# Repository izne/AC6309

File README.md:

# AC6309 Platform
A minimalistic industrial computer core, based on Motorola 6809 architecture.

## Purpose
Proof of concept custom 8-bit industrial computer with minimal device count implementation. Modular, low-power design, allowing easy expansion and customization per use case.

## Dedication
AC29 is dedicated to my beloved father.

## AC29 projected configuration

## Prototype build 
* CPU: HD63B09 @ 1.8432MHz
* RAM: 32KB W24257A
* ROM: 8KB 28C256 (2x ROMs)
* UART: HD63B50 (1MBps) on FT23 USB Serial
* Address decoding: 74HCT00 & 74HCT138
* Expansion: 1x 40-pin header for expansion board with 3 slots mapped at $8000, $9000 and $B000
* Power over USB

## Example physical layout

## PCB Updates
Current state of PCB design:

## System memory map
|Address range|Device|Size|
|-------------|------|----|
|$0000-$7FFF|RAM|32KB|
|$8000-$8FFF|Extension port #1|4KB|
|$9000-$9FFF|Extension port #2|4KB|
|$A000-$AFFF|UART|4KB|
|$B000-$BFFF|Extension port #3|4KB|
|$C000-$FFFF|ROM|16KB|

The 32KB of RAM is allocated from the bottom of the address range $0000 to $7FFF.
The ROM is allocated at top 8KB of the address space starting $C000 to $DFFF.

The I/O mapping is allowing compatibility with existing BIOS images having ACIA on address 0xA000. 

## Writing the ROM image
Using the combination ROM image in Intel HEX format it needs first be turned into a binary image to be written to the EEPROM.
> objcopy -I ihex -O binary combined.hex combined.bin

Write the resulting .bin file using the specially created EEPROM programmer for AT28C-series EEPROMs. Or any other.
> promdude.exe -f combined.bin

As a note, burning the combined.bin (16K) onto 32K 28C256 has to be at the correct half. Optionally, a copy of combined.bin twice into the chip will do as well.

## ROM switching
As the firmware is 16K and 28C256 (32K) chips are nowadays more accesible, two firmware images could be stored in the full 32K capacity of the chip. A ROM switching key to be implemented on the board, to switch the higher or lower part of the chip to be "visible" (A14) at boot.

## Communication
The system communicates with a terminal via USB serial connection using the included ACIA device and its UART capability, coupled with an FTDI232 header. Terminal serial port settings: 115200 baud, 8n1, no hardware handshake yet.

## Software checklist
- [x] Run ASSIST09 and Extended BASIC
- [x] Write basic program (asm)
- [x] Cross-compile on host machine
- [x] Easy program transer via ASSIST09 Load (S19)
- [ ] Use of high level C code (CMOC)

## Hardware checklist
- [x] Breadboard prototype running
- [x] Revision 1 completion and PCB fabrication
- [ ] Extended addressing ("A" - four internal devices, "B" - four external devices)
- [ ] Expansion board with easy coupling
- [ ] 28C16-based address decoder
- [ ] Expansion card: Am9511 card (Am9511, 3MHz osc, 5to12Vbuck)
- [ ] Expansion card: Tape interface
- [ ] Expansion card: TMP68681 / 2x RS232 / 115200 bps (own osc)
- [ ] Expansion card: Ethernet adapter (ENC28J60)
- [ ] Expansion card: SAA1099 + TDA2822 audio interface
- [ ] Expansion card: VGA and PS/2 (Arduino)
- [ ] Expansion card: VGA and PS/2 (MC6845/HD6321)
- [ ] Expansion card: VGA (EF9367)
- [ ] Expansion card: Keyboard controller (XT, AT, PS/2, USB)

## Toolchain
* [ASM6809](https://www.6809.org.uk/asm6809/doc/asm6809.shtml)
* [A09](https://github.com/Arakula/A09)
* [AS09](https://gitlab.com/dfffffff/as09)
* [LWTOOLS-4.20](http://www.lwtools.ca/)
* [CMOC](http://perso.b2b2c.ca/~sarrazip/dev/cmoc.html)
* [MillFork](https://github.com/KarolS/millfork)

## Emulators
* [6809 online assembler](http://6809.uk/)
* [XRoar](https://www.6809.org.uk/xroar/online/)

- - - 
#### Prerequisites
The schematics and PCB design is made with [KiCad](http://kicad.org)

#### References and inspiration:
* [sbc689 by Jeff Tranter](https://github.com/jefftranter/6809)
* [6809 computer by Grant Searle](http://searle.x10host.com/6809/Simple6809.html)
* [HB6809 by Lindoran](https://github.com/lindoran/HB6809)
* [OMEN Kilo](https://github.com/omenmicro/kilo)
* [Chip Labels by Grant Searle](http://searle.x10host.com/labels/ChipLabels.pdf)

### Some great oldschool books:

* .pdf)

* .pdf)

* .pdf)

* .pdf)

* [The 6309 Book](https://colorcomputerarchive.com/repo/Documents/Books/The%206309%20Book%20(Burke%20&%20Burke).pdf)

https://colorcomputerarchive.com/repo/Documents/Books/Programming%20the%206809%20(Rodney%20Zaks%20and%20William%20Labiak).pdf

https://www.chibiakumas.com/6809/

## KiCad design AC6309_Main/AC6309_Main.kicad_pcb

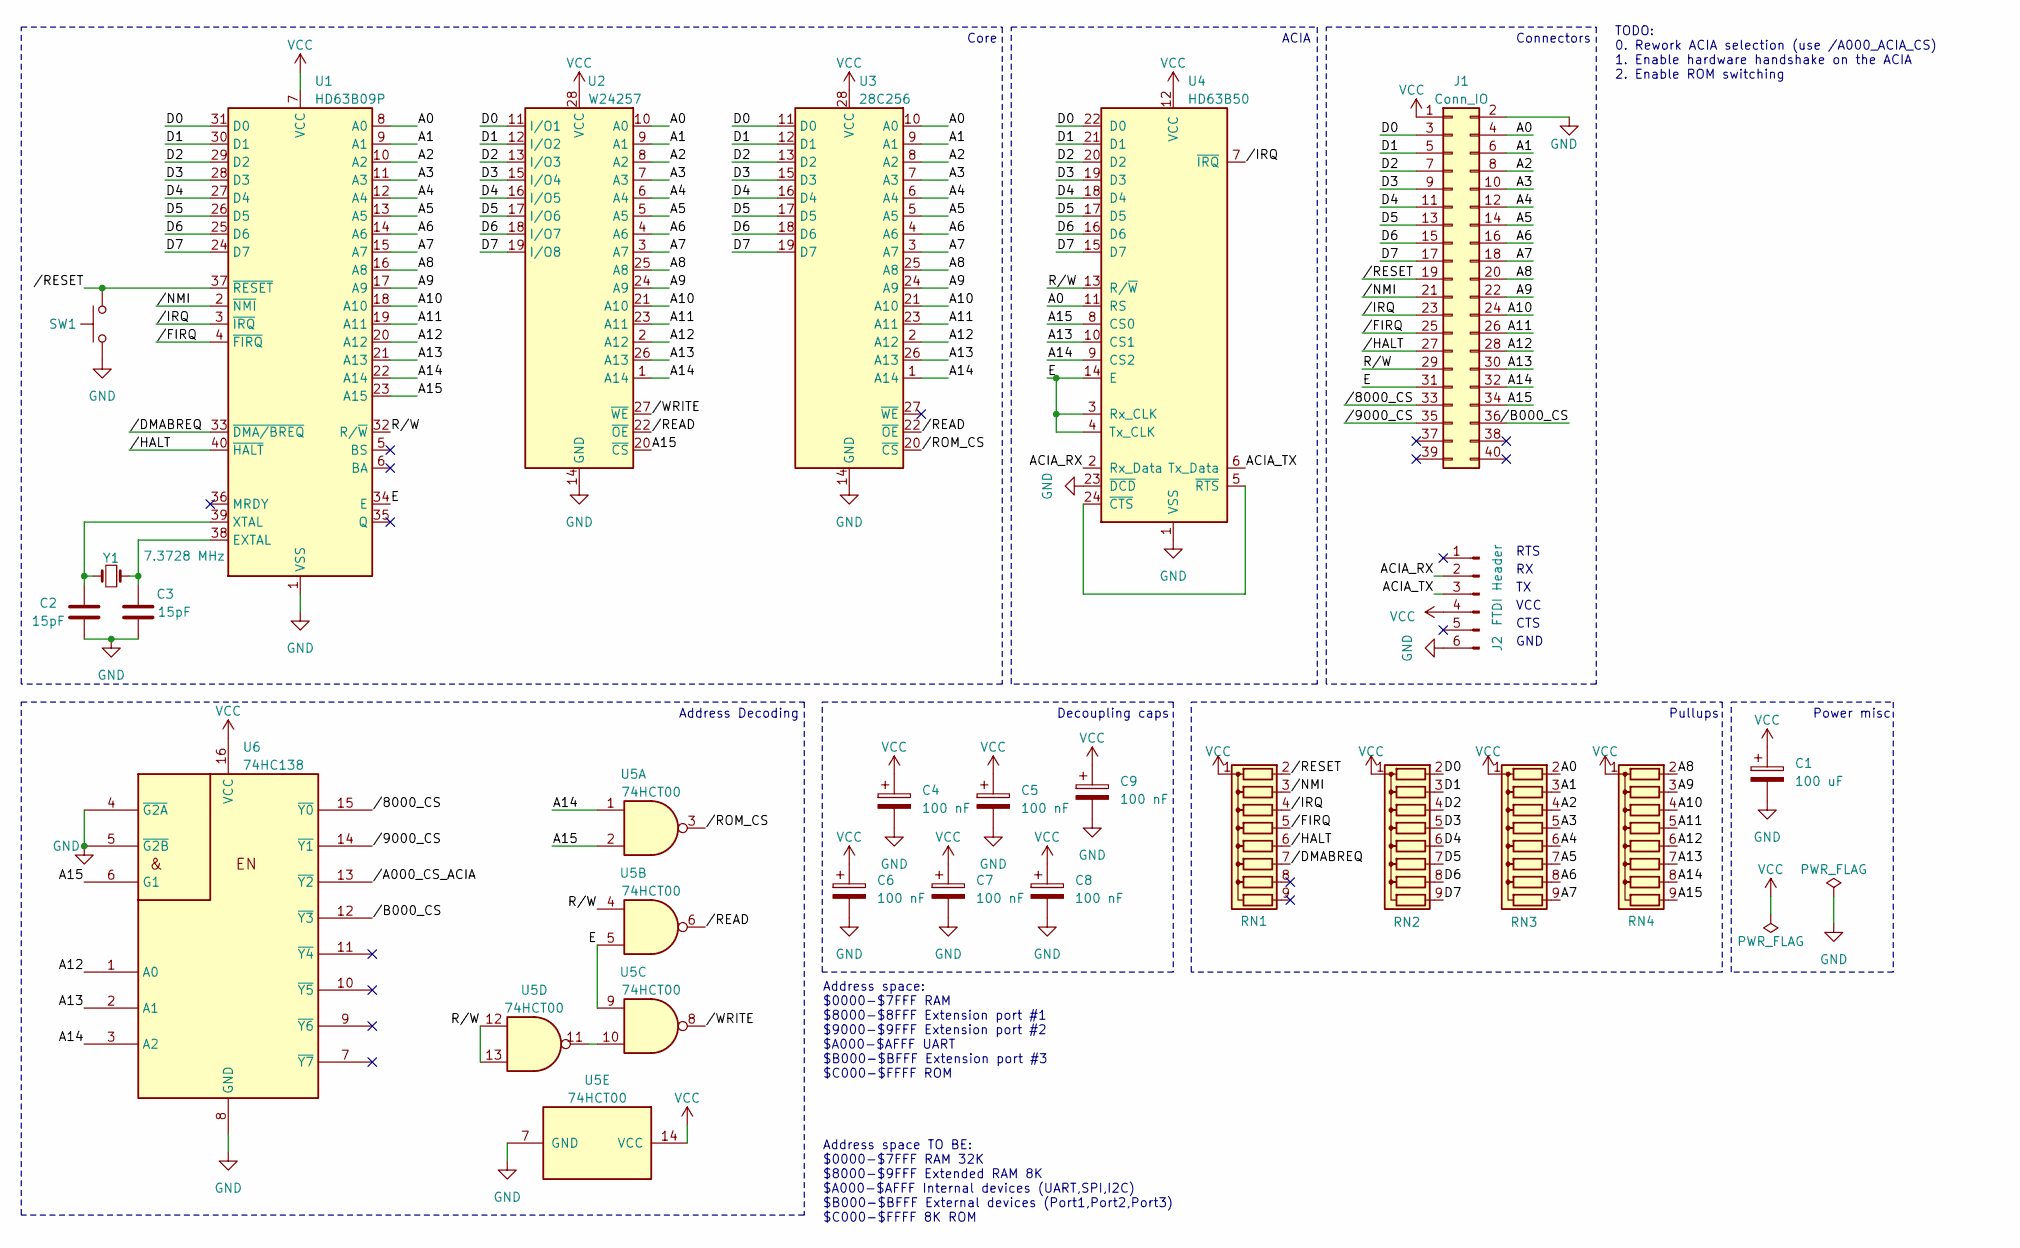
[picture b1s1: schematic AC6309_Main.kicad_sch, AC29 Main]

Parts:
C1: 100 uF; CP_Radial_D8.0mm_P2.50mm
C2, C3: 15pF; C_Disc_D3.0mm_W1.6mm_P2.50mm
C4, C5, C6, C7, C8, C9: 100 nF; C_Disc_D3.0mm_W2.0mm_P2.50mm
J1: Conn_IO; PinHeader_2x20_P2.54mm_Vertical
J2: FTDI Header; PinSocket_1x06_P2.54mm_Vertical
RN1, RN2, RN3, RN4: R_Network08; R_Array_SIP9
SW1: Reset; SW_Tactile_Straight_KSL0Axx1LFTR
U1: HD63B09P; DIP-40_W15.24mm_Socket
U2: W24257; DIP-28_W7.62mm_Socket
U3: 28C256; DIP-28_W15.24mm_Socket
U4: HD63B50; DIP-24_W15.24mm_Socket
U5: 74HCT00; DIP-14_W7.62mm_Socket
U6: 74HC138; DIP-16_W7.62mm_Socket
Y1: 7.3728 MHz; Crystal_HC49-4H_Vertical

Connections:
/A0: J1.4, RN3.2 (R1), U1.8 (A0), U2.10 (A0), U3.10 (A0), U4.11 (RS)
/A1: J1.6, RN3.3 (R2), U1.9 (A1), U2.9 (A1), U3.9 (A1)
/A2: J1.8, RN3.4 (R3), U1.10 (A2), U2.8 (A2), U3.8 (A2)
/A3: J1.10, RN3.5 (R4), U1.11 (A3), U2.7 (A3), U3.7 (A3)
/A4: J1.12, RN3.6 (R5), U1.12 (A4), U2.6 (A4), U3.6 (A4)
/A5: J1.14, RN3.7 (R6), U1.13 (A5), U2.5 (A5), U3.5 (A5)
/A6: J1.16, RN3.8 (R7), U1.14 (A6), U2.4 (A6), U3.4 (A6)
/A7: J1.18, RN3.9 (R8), U1.15 (A7), U2.3 (A7), U3.3 (A7)
/A8: J1.20, RN4.2 (R1), U1.16 (A8), U2.25 (A8), U3.25 (A8)
/A9: J1.22, RN4.3 (R2), U1.17 (A9), U2.24 (A9), U3.24 (A9)
/A10: J1.24, RN4.4 (R3), U1.18 (A10), U2.21 (A10), U3.21 (A10)
/A11: J1.26, RN4.5 (R4), U1.19 (A11), U2.23 (A11), U3.23 (A11)
/A12: J1.28, RN4.6 (R5), U1.20 (A12), U2.2 (A12), U3.2 (A12), U6.1 (A0)
/A13: J1.30, RN4.7 (R6), U1.21 (A13), U2.26 (A13), U3.26 (A13), U4.10 (CS1), U6.2 (A1)
/A14: J1.32, RN4.8 (R7), U1.22 (A14), U2.1 (A14), U3.1 (A14), U4.9 (CS2), U5.1, U6.3 (A2)
/A15: J1.34, RN4.9 (R8), U1.23 (A15), U2.20 (~CS), U4.8 (CS0), U5.2, U6.6 (G1)
/ACIA_RX: J2.2, U4.2 (Rx_Data)
/ACIA_TX: J2.3, U4.6 (Tx_Data)
/D0: J1.3, RN2.2 (R1), U1.31 (D0), U2.11 (I/O1), U3.11 (D0), U4.22 (D0)
/D1: J1.5, RN2.3 (R2), U1.30 (D1), U2.12 (I/O2), U3.12 (D1), U4.21 (D1)
/D2: J1.7, RN2.4 (R3), U1.29 (D2), U2.13 (I/O3), U3.13 (D2), U4.20 (D2)
/D3: J1.9, RN2.5 (R4), U1.28 (D3), U2.15 (I/O4), U3.15 (D3), U4.19 (D3)
/D4: J1.11, RN2.6 (R5), U1.27 (D4), U2.16 (I/O5), U3.16 (D4), U4.18 (D4)
/D5: J1.13, RN2.7 (R6), U1.26 (D5), U2.17 (I/O6), U3.17 (D5), U4.17 (D5)
/D6: J1.15, RN2.8 (R7), U1.25 (D6), U2.18 (I/O7), U3.18 (D6), U4.16 (D6)
/D7: J1.17, RN2.9 (R8), U1.24 (D7), U2.19 (I/O8), U3.19 (D7), U4.15 (D7)
/E: J1.31, U1.34 (E), U4.3 (Rx_CLK), U4.4 (Tx_CLK), U4.14 (E), U5.5, U5.9
/R/W: J1.29, U1.32 (R/~W), U4.13 (R/~W), U5.4, U5.12, U5.13
//8000_CS: J1.33, U6.15 (~Y0)
//9000_CS: J1.35, U6.14 (~Y1)
//A000_CS_ACIA: U6.13 (~Y2)
//B000_CS: J1.36, U6.12 (~Y3)
//DMABREQ: RN1.7 (R6), U1.33 (~DMA/BREQ)
//FIRQ: J1.25, RN1.5 (R4), U1.4 (~FIRQ)
//HALT: J1.27, RN1.6 (R5), U1.40 (~HALT)
//IRQ: J1.23, RN1.4 (R3), U1.3 (~IRQ), U4.7 (~IRQ)
//NMI: J1.21, RN1.3 (R2), U1.2 (~NMI)
//READ: U2.22 (~OE), U3.22 (~OE), U5.6
//RESET: J1.19, RN1.2 (R1), SW1.2, U1.37 (~RESET)
//ROM_CS: U3.20 (~CS), U5.3
//WRITE: U2.27 (~WE), U5.8
GND: C1.2, C2.2, C3.2, C4.2, C5.2, C6.2, C7.2, C8.2, C9.2, J1.2, J2.6, SW1.1, U1.1 (VSS), U2.14 (GND), U3.14 (GND), U4.1 (VSS), U4.23 (~DCD), U5.7 (GND), U6.4 (~G2A), U6.5 (~G2B), U6.8 (GND)
unnamed: C3.1, U1.38 (EXTAL), Y1.1
unnamed: C2.1, U1.39 (XTAL), Y1.2
unnamed: U4.5 (~RTS), U4.24 (~CTS)
unnamed: U5.10, U5.11
VCC: C1.1, C4.1, C5.1, C6.1, C7.1, C8.1, C9.1, J1.1, J2.4, RN1.1 (common), RN2.1 (common), RN3.1 (common), RN4.1 (common), U1.7 (VCC), U2.28 (VCC), U3.28 (VCC), U4.12 (VCC), U5.14 (VCC), U6.16 (VCC)

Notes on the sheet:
Pullups
CTS
Power misc
Connectors
Address Decoding
Address space: $0000-$7FFF RAM $8000-$8FFF Extension port #1 $9000-$9FFF Extension port #2 $A000-$AFFF UART $B000-$BFFF Extension port #3 $C000-$FFFF ROM
TODO: 0. Rework ACIA selection (use /A000_ACIA_CS) 1. Enable hardware handshake on the ACIA 2. Enable ROM switching
GND
RTS
Core
Address space TO BE: $0000-$7FFF RAM 32K $8000-$9FFF Extended RAM 8K $A000-$AFFF Internal devices (UART,SPI,I2C) $B000-$BFFF External devices (Port1,Port2,Port3) $C000-$FFFF 8K ROM
Decoupling caps
VCC
ACIA

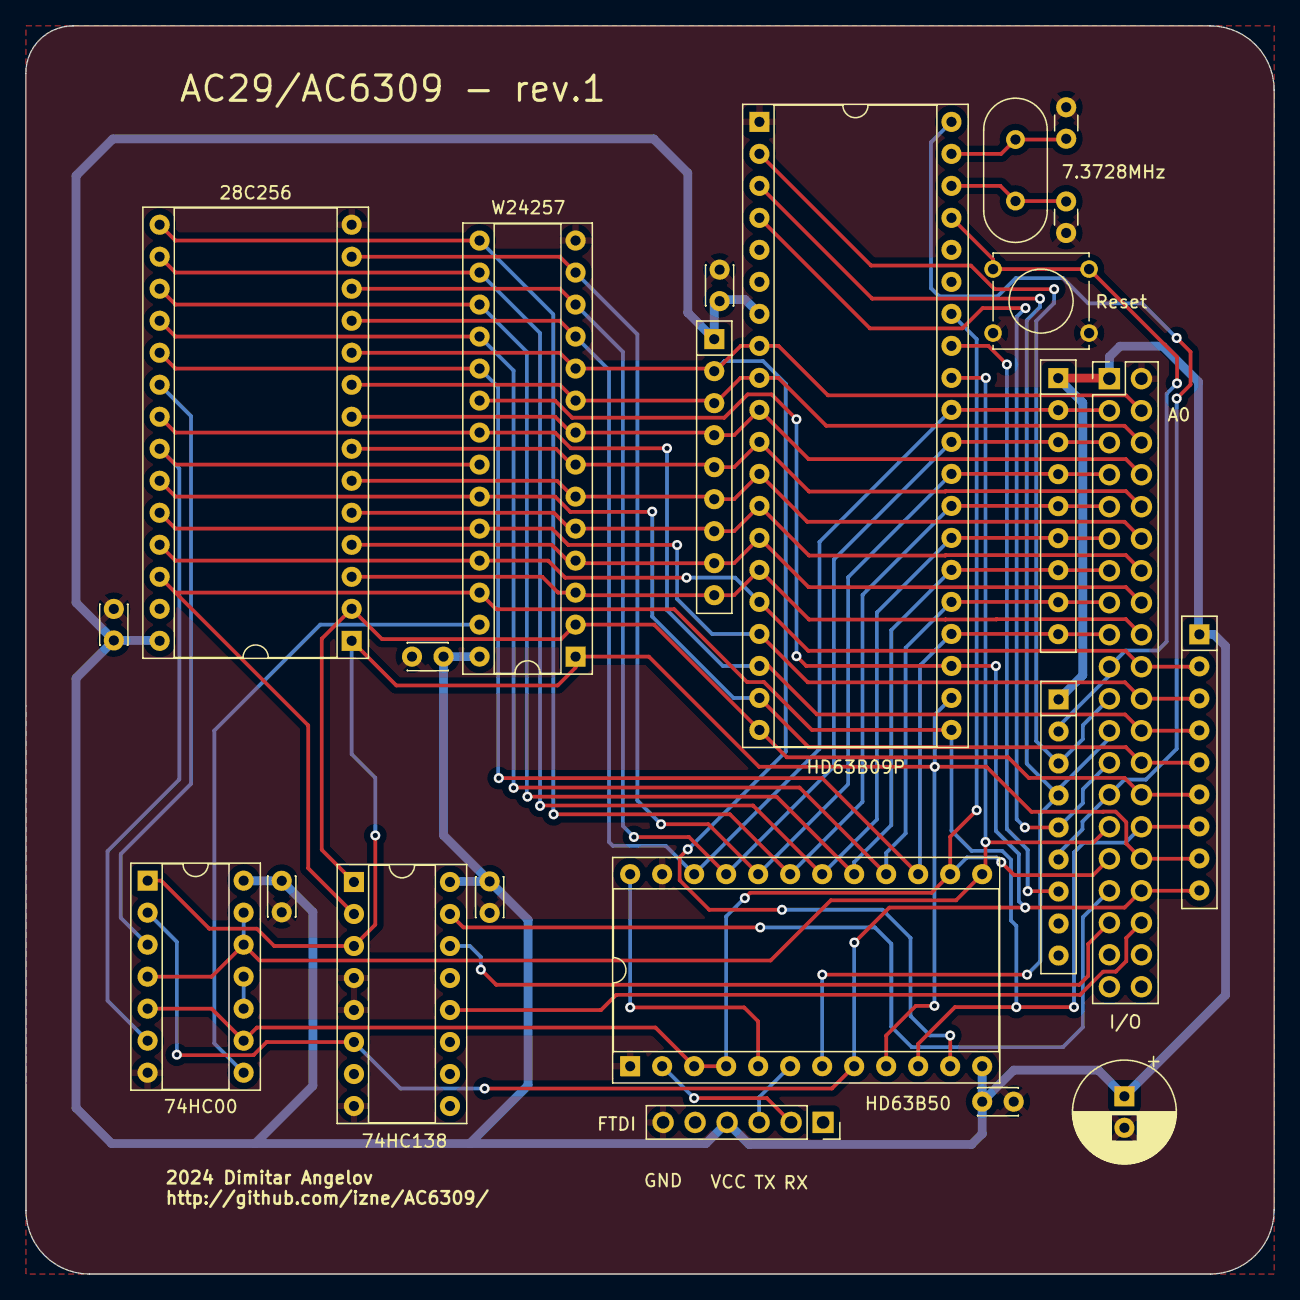
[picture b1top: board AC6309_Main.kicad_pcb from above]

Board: 2 copper layers, 99.1 x 99.1 mm, 23 parts (0 on the bottom side), 46 nets.

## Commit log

2023-03-05 Steigero init
2023-03-05 gitign
2023-03-05 Datasheets, readme and some screenshots
2023-03-05 Cleaning
2023-03-05 Readme update
2023-03-06 Adding 74HC138 to the address decoder
2023-03-06 Update renders
2023-03-09 Added resistor networks. Updated PCB layout. Added temporary freeroute traces.
2023-03-23 Replaced UART. Updates on Readme .
2023-06-01 Schematics revision 1, Digital file, etc.
2023-11-27 Readme updates, extended basic examples, cpu check
2023-11-27 Updates to readme
2023-11-27 md upd
2023-11-27 Updates on readme
2023-12-05 Put some images and examples
2023-12-05 Typos and more images
2023-12-05 KiCad sync
2023-12-05 Update of layout diagram
2023-12-05 Addressing note
2023-12-05 Update layouts and add book links
2023-12-05 Update layout images
2023-12-09 Some renders update
2024-04-15 SCH and PCB updats. DRC issues fixed.
2024-05-17 First working version of the AC29 firmware!
2025-01-03 Updates from 2024. Rev1 going in production.
2025-06-06 Added PROM Decoder. Added BAS and ASM examples.
2025-06-06 Updates on PROM decoder
2025-06-06 Updates on the documentation of the PROM decoder
2025-06-06 Updated PROM decoder logic to use A15
2025-06-07 Updated PROM Dec to use only 11-bit address lines
